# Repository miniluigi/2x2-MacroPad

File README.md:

# 2x2 MacroPad
 First PCB Design

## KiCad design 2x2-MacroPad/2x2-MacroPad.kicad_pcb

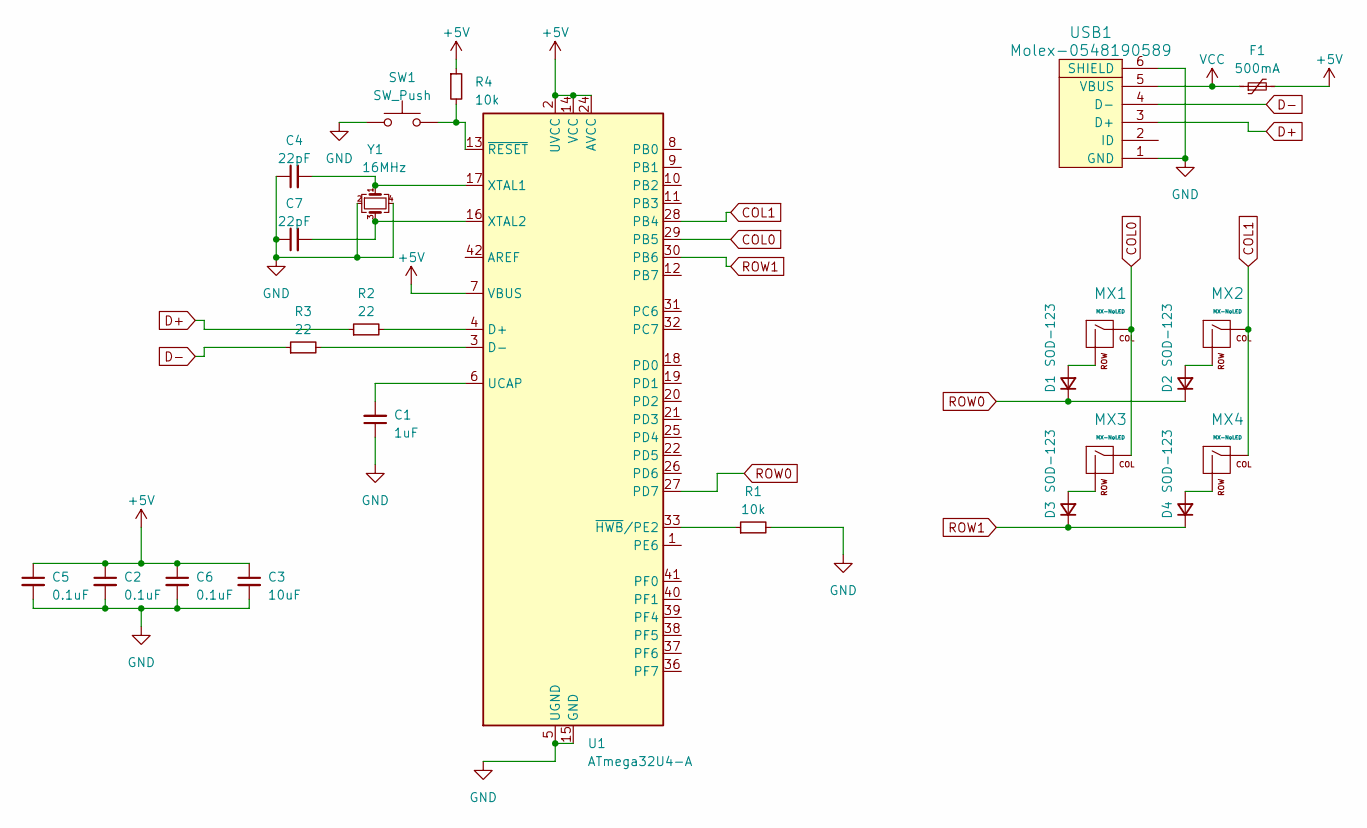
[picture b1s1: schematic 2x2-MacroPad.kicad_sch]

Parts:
C1: 1uF; C_0805_2012Metric
C2, C5, C6: 0.1uF; C_0805_2012Metric
C3: 10uF; C_0805_2012Metric
C4, C7: 22pF; C_0805_2012Metric
D1, D2, D3, D4: SOD-123; D_SOD-123
F1: 500mA; Fuse_1206_3216Metric
MX1, MX2, MX3, MX4: MX-NoLED; MX-1U-NoLED
R1, R4: 10k; R_0805_2012Metric
R2, R3: 22; R_0805_2012Metric
SW1: SW_Push; SKQG-1155865
U1: ATmega32U4-A; TQFP-44_10x10mm_P0.8mm
USB1: Molex-0548190589
Y1: 16MHz; Crystal_SMD_3225-4Pin_3.2x2.5mm_HandSoldering

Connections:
+5V: C2.1, C3.1, C5.1, C6.1, F1.2, R4.1, U1.2 (UVCC), U1.7 (VBUS), U1.14 (VCC), U1.24 (AVCC), U1.34 (VCC), U1.44 (AVCC)
COL0: MX1.1 (COL), MX3.1 (COL), U1.29 (PB5)
COL1: MX2.1 (COL), MX4.1 (COL), U1.28 (PB4)
D+: R2.1, USB1.3 (D+)
D-: R3.1, USB1.4 (D-)
GND: C1.1, C2.2, C3.2, C4.1, C5.2, C6.2, C7.1, R1.2, SW1.1, U1.5 (UGND), U1.15 (GND), U1.23 (GND), U1.35 (GND), U1.43 (GND), USB1.1 (GND), USB1.6 (SHIELD), Y1.2, Y1.4
unnamed: D1.2 (A), MX1.2 (ROW)
unnamed: D2.2 (A), MX2.2 (ROW)
unnamed: D3.2 (A), MX3.2 (ROW)
unnamed: D4.2 (A), MX4.2 (ROW)
unnamed: R2.2, U1.4 (D+)
unnamed: R3.2, U1.3 (D-)
unnamed: C1.2, U1.6 (UCAP)
unnamed: C4.2, U1.17 (XTAL1), Y1.1
unnamed: C7.2, U1.16 (XTAL2), Y1.3
unnamed: R1.1, U1.33 (~HWB/PE2)
unnamed: R4.2, SW1.2, U1.13 (~RESET)
ROW0: D1.1 (K), D2.1 (K), U1.27 (PD7)
ROW1: D3.1 (K), D4.1 (K), U1.30 (PB6)
VCC: F1.1, USB1.5 (VBUS)

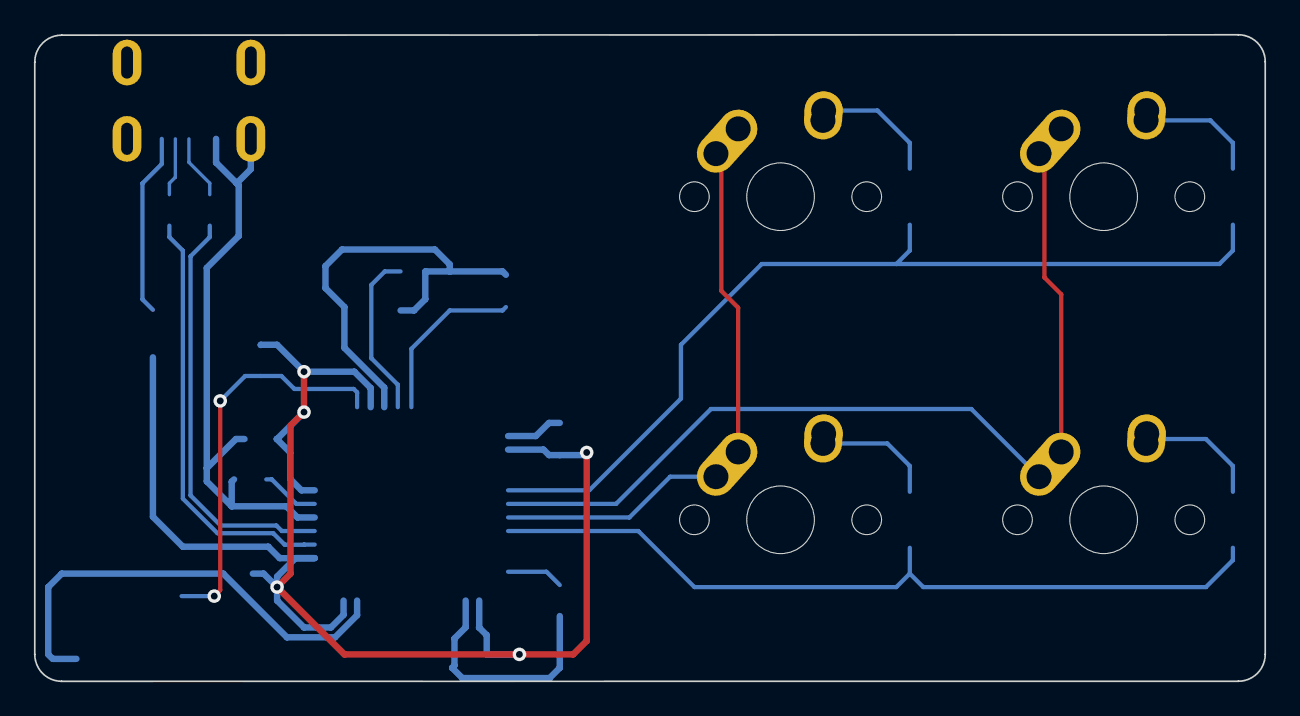
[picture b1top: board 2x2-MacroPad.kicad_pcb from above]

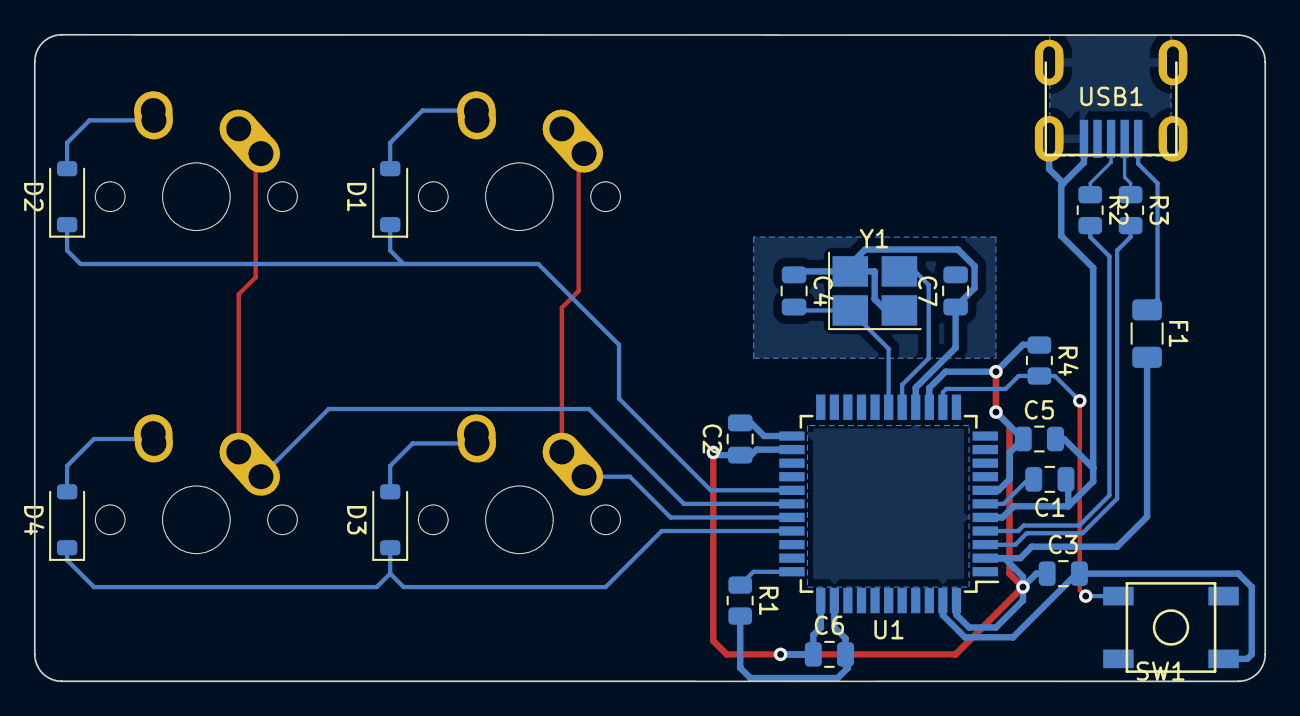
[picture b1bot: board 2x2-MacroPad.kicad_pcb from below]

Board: 2 copper layers, 72.6 x 38.1 mm, 24 parts (20 on the bottom side), 20 nets.

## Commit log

2023-05-17 Initialize project
2023-05-17 Add submodules
2023-05-17 Changed Libraries in KiCad
2023-05-17 Started to add to atmega32
2023-05-19 Finished Schematic
2023-05-19 Started PCB routing
2023-05-22 Routed everything except keys
2023-05-22 Finished Routing
2023-05-24 Finished
